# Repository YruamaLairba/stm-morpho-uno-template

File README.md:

# stm-morpho-uno-template
KiCad Template for STM32 Nucleo-64 Expansion Boards including Arduino Uno
headers. Based on https://github.com/mobilinkd/stm-morpho-template.

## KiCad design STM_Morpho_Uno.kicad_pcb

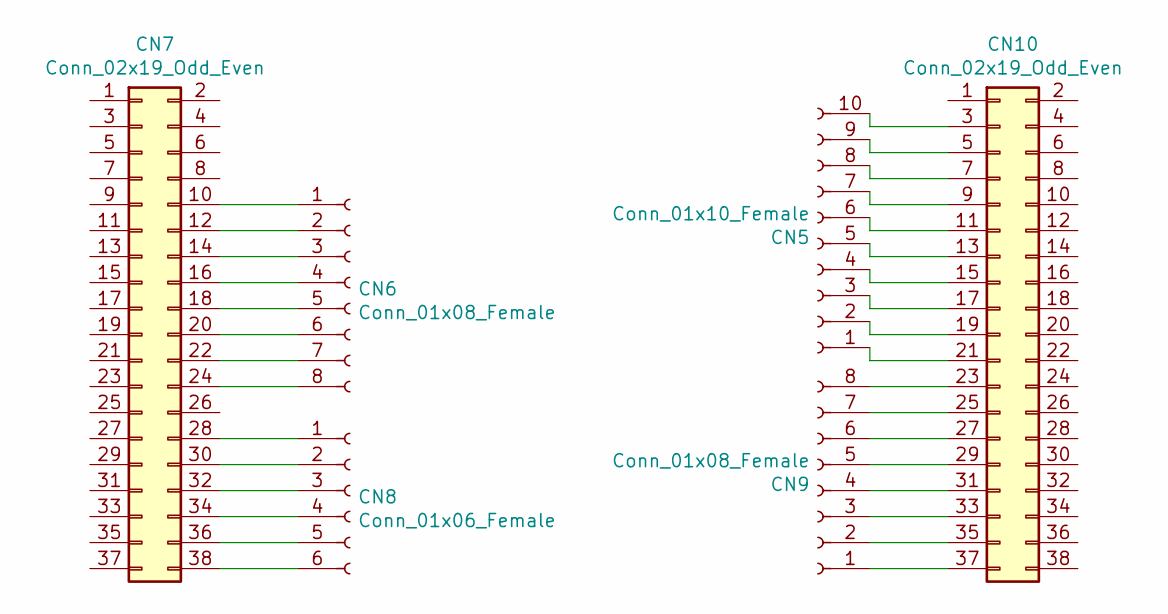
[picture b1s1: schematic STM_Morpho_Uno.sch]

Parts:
CN5: Conn_01x10_Female; PinSocket_1x10_P2.54mm_Vertical
CN6, CN9: Conn_01x08_Female; PinSocket_1x08_P2.54mm_Vertical
CN7, CN10: Conn_02x19_Odd_Even; PinSocket_2x19_P2.54mm_Vertical
CN8: Conn_01x06_Female; PinSocket_1x06_P2.54mm_Vertical

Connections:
unnamed: CN6.1, CN7.10
unnamed: CN6.2, CN7.12
unnamed: CN6.3, CN7.14
unnamed: CN6.4, CN7.16
unnamed: CN6.5, CN7.18
unnamed: CN6.6, CN7.20
unnamed: CN6.7, CN7.22
unnamed: CN6.8, CN7.24
unnamed: CN7.28, CN8.1
unnamed: CN7.30, CN8.2
unnamed: CN7.32, CN8.3
unnamed: CN7.34, CN8.4
unnamed: CN7.36, CN8.5
unnamed: CN7.38, CN8.6
unnamed: CN5.10, CN10.3
unnamed: CN5.9, CN10.5
unnamed: CN5.8, CN10.7
unnamed: CN5.7, CN10.9
unnamed: CN5.6, CN10.11
unnamed: CN5.5, CN10.13
unnamed: CN5.4, CN10.15
unnamed: CN5.3, CN10.17
unnamed: CN5.2, CN10.19
unnamed: CN5.1, CN10.21
unnamed: CN9.8, CN10.23
unnamed: CN9.7, CN10.25
unnamed: CN9.6, CN10.27
unnamed: CN9.5, CN10.29
unnamed: CN9.4, CN10.31
unnamed: CN9.3, CN10.33
unnamed: CN9.2, CN10.35
unnamed: CN9.1, CN10.37

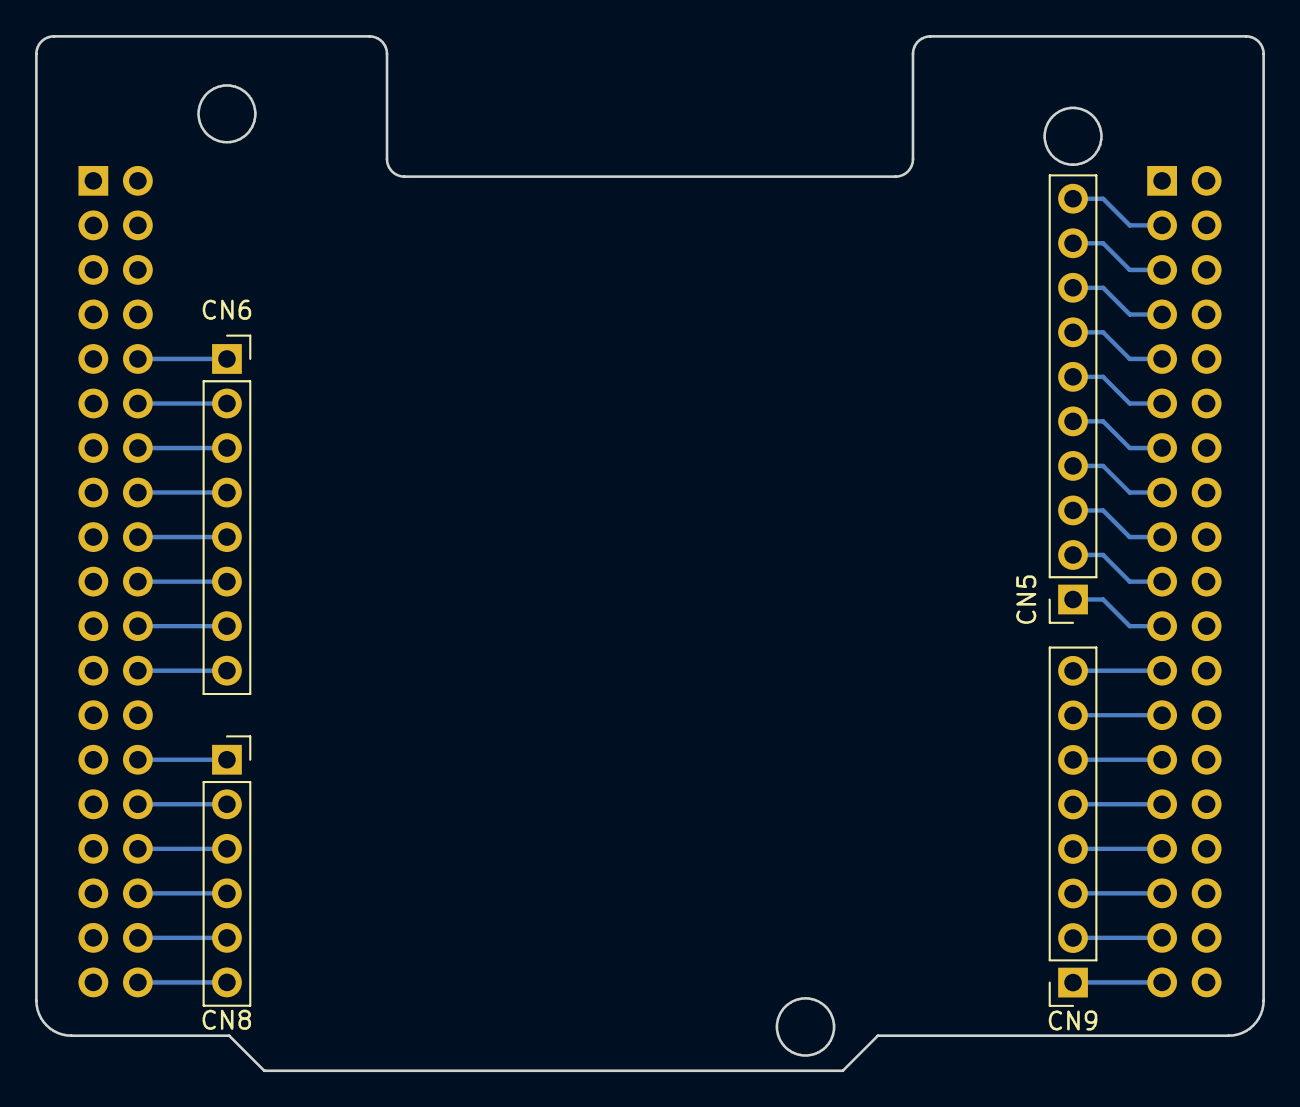
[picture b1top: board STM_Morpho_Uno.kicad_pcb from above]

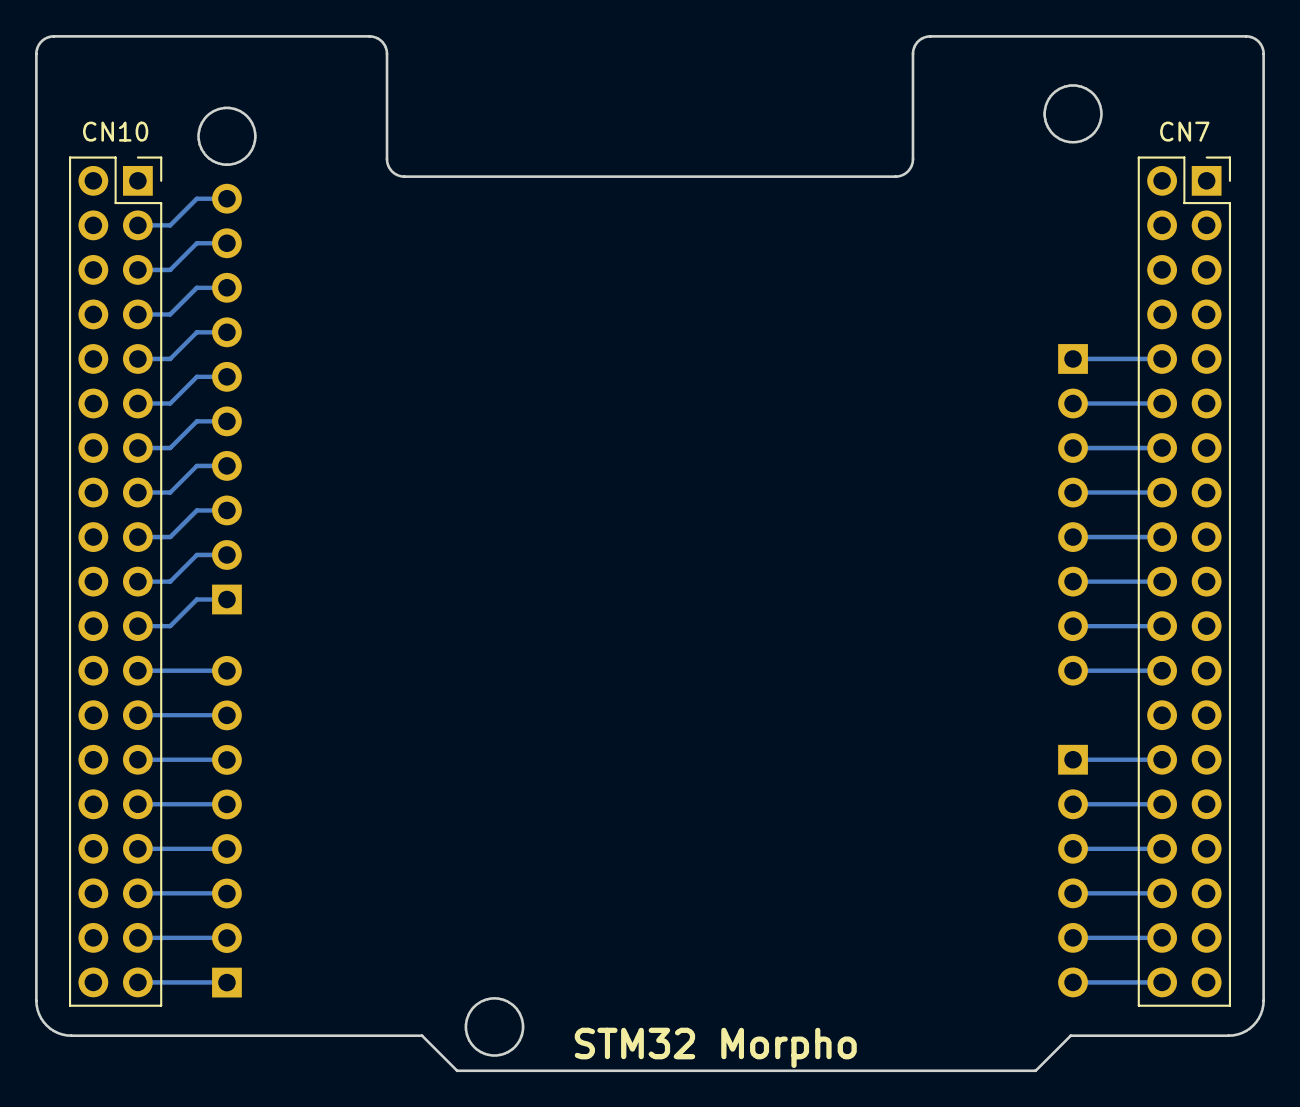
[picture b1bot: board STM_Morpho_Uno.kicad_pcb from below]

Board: 2 copper layers, 70.0 x 59.0 mm, 6 parts (2 on the bottom side), 32 nets.

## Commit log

2021-04-03 initial commit
    map arduino connector footprint
    add arduino socket and link connectors
    add meta
    LICENSE and README
    change tmplate name from kicad view
2021-04-07 fix, right uno connector where upside down compared to datasheet
